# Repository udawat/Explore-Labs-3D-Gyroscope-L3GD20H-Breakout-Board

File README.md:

# Explore Labs 3D Gyroscope L3GD20H Breakout Board
## Overview

[Explore Labs 3D Gyroscope L3GD20H Breakout Board](http://www.explorelabs.com/explore-labs-3d-gyroscope-l3gd20h-breakout-board-5v-ready-with-voltage-regulator "Explore Labs 3D Gyroscope L3GD20H Breakout Board") is based on ST L3GD20H three-axis gyroscope, which measures the angular rates of rotation about the roll (X), pitch (Y), and yaw (Z) axes. Angular velocity measurements with a configurable range of ±245°/s, ±500°/s, or ±2000°/s can be read through a digital I2C or SPI interface.

The carrier board includes a low-dropout linear voltage regulator that provides the 3.3 V required by the L3GD20H, which allows the sensor to be powered from 2.5 V to 5.5 V. The regulator output is available on the 3Vo pin which can supply approx. 150 mA to external devices.

The breakout board also includes a circuit that shifts the two I2C lines or all four SPI lines (clock, data-in/out and chip select) to the same logic voltage level as the supplied VIN, making it simple to interface the board with 5V systems; and the board’s 0.1″ pin spacing makes it easy to use with standard solderless breadboards and 0.1″ perfboards. The board ships fully populated with its SMD components, including the L3GD20H, as shown in the product picture.

## Features of Explore Labs 3D Gyroscope L3GD20H Breakout Board:
* Wide supply voltage - 2.5V to 5V
* Level shifted IO lines for easy interfacing to high voltage boards like Arduino Uno, Mega, Leonardo, etc.
* All pins of the L3GD20H sensor are available like INT1, INT2 (DRDY) and DEN (Data Enable)
* Layout takes care of keeping the area below the sensor free from any active current carrying trace or a power or ground plane
* Capacitors with low ESR characteristics are used for decoupling on both VDD and VDDIO power inputs
* Open Source Hardware
* Designed, Assembled and Made in India

## Features of L3GD20H sensor IC:
* Extended operating temperature range (from -40 °C to 85 °C)
* Low power consumption
* Embedded power-down
* Sleep mode
* Fast turn-on and wake-up
* Three selectable full scales up to 2000 dps (degrees per second)
* 16 bit rate value data output
* 8 bit temperature data output
* I2C/SPI digital output interface
* 2 dedicated lines (1 interrupt, 1 data ready)
* User enable integrated high-pass filters
* Embedded temperature sensor
* Embedded 32 levels of 16 bit data output FIFO
* High shock survivability

## Specifications:
* Input Voltage: 2.5V to 5V
* 5V Ready IOs: Level shifted IO lines for easy interfacing to incompatible voltage boards
* Digital Output: Inter Integrated Circuit (I2C/IIC) or Serial Peripheral Interface (SPI)
* Regulator Pin - Provides 3.3V Out at 150mA (when 3.6V < VIN < 5V) else provides voltage ~equal to VIN
* Dimensions: 20.4 mm x 20 mm
* Weight: 2 grams

## Applications:
* Gaming and virtual reality input devices
* Motion control with MMI (man-machine interface)
* GPS navigation systems
* Appliances and robotics

## Output Format:
Provides individual readings for each axis in degrees per decond (dps). These readings may be used separately or together with an Accelerometer for 3D calculations like calculating euler angles (roll, pitch, yaw) and other complex orientation calculationsfor Inertial Measurement Units (IMU).

## Pinout Table for Explore Labs 3D Gyroscope L3GD20H Breakout Board
|Pin|5V Safe?   |Function|
|---|-----------|--------|
|VIN|Yes|**Input Voltage** Pin: 2.5V to 5.0V (depending on Master device being used as mentioned in later connection sections and tables below)|
|3Vo|Not Applicable|This is the output pin of the onboard 3.3V Voltage Regulator. It provides a clean and regulated 3.3V output to the sensor IC. It can also be used by the user to provide power to external devices or sensors. Maximum current that can be sourced easily would be approximately 125mA to 150mA after leaving some room for the on board sensor IC|
|GND|Not Applicable|Ground Connection. Connect this pin to the master device's ground pin or to any externally powered devices from onboard regulator|
|SDI/SDA|Yes. Bidirectional MOSFET with 4K7 pull-ups|This pin has dual functions - **Serial Data Input** (for SPI) or **Serial Data** (for I2C). In case of SPI, it can also be called as Master Out Slave In (MOSI)|
|SCK/SCL|Yes. Bidirectional MOSFET with 4K7 pull-ups|This pin is the **Serial Clock** input pin. It is common for both SPI and I2C interfaces|
|SDO/ADR|Yes. Only a 4K7 pull-up resistor needed as this is an output pin|This pin has dual functions - **Serial Data Output** (for SPI) or **Address Select** (for I2C). Also called as SA0. In case of SPI, it can also be called as Master In Slave Out (MOSI). In case of I2C, this pin may be pulled LOW or grounded for selecting an alternate address to avoid address conflicts with similar I2C devices. The change will have to be updated in code as well. Leave unconnected if no change in address required for I2C|
|CS|Yes. Bidirectional MOSFET with 4K7 pull-ups|**Chip Select** or Slave Select pin. By default, it is pulled HIGH using an onboard 4K7 pull-up resistor. This sets the default mode of communication for the sensor IC as I2C. For SPI, this pin acts as the chip select pin to communicate with an SPI master device. Leave unconnected when using I2C|
|DEN|No. Take proper care when interfacing with devices that have higher voltage levels. This pin is not 5V tolerant!|**Data Enable** input pin. The L3GD20H allows external trigger level recognition through enabling the EXTRen (bit7) and LVLen (bit6) bits in CTRL2 (21h) register and the IMPen (bit3) bit of CTRL4 register. Three different modes can be used: level-sensitive, pulse-sensitive and edge-sensitive trigger. More detailed explanation can be found in [Section 3.5 of ST Application Note AN4506](http://www.st.com/resource/en/application_note/dm00119037.pdf "ST Application Note - L3GD20H: 3-axis digital output gyroscope")|
|INT1|No|Interrupt output pin. The L3GD20H interrupt signal can be configured in a very flexible way allowing to recognize independent rotations of the X, Y and Z-axis. That signal can be driven to the INT1 pin. The device may be configured to generate interrupt signals by detecting an independent wake-up event. Thresholds and timing of the interrupt generator are programmable by the end user on the fly. More detailed explanation can be found in [Section 5 of ST Application Note AN4506](http://www.st.com/resource/en/application_note/dm00119037.pdf "ST Application Note - L3GD20H: 3-axis digital output gyroscope")|
|INT2|No|Second Interrupt output pin. This pin is dedicated to DRDY and FIFO interrupts. **DRDY Interrupt**: The device may be configured to have one HW signal to determine when a new set of measurement data is available for reading. This signal is represented by the XYZDA bit of the STATUS register. The signal can be driven to the DRDY/INT2 pin. **FIFO Interrupt**: The device may be configured to generate an interrupt on FIFO Threshold, FIFO Overrun or FIFO Empty event. For more details, refer to above application note from ST. More detailed explanation can be found in [Section 3.3 and Section 5.1 of ST Application Note AN4506](http://www.st.com/resource/en/application_note/dm00119037.pdf "ST Application Note - L3GD20H: 3-axis digital output gyroscope")|

## Connections with various development boards are explained below:

The carrier board supports both I2C as well as SPI method of communication with a host microcontroller. The communication mode is selected by pulling the CS pin HIGH or LOW. By default, the CS pin is pulled HIGH through a 4.7 kΩ resistor on the board. This makes I2C communication the default method to talk to this carrier board.

**I2C Communication**: By default, I2C communication is implemented. The Explore Labs 3D Gyroscope L3GD20H Breakout Board can be configured and its angular velocity readings can be queried through the I2C bus. Level shifters on the I2C clock (SCL) and data (SDA) lines enable I2C communication with microcontrollers operating at the same voltage as VIN (2.5V to 5V). A detailed explanation of the I2C interface on the L3GD20H can be found in its [datasheet][1] and more detailed information about I2C Protocol in general can be found in [NXP’s I2C-bus specification manual][2].

**I2C Address**: In I2C mode, the gyro’s 7-bit slave address has its least significant bit (LSb) determined by the voltage on the SDO/ADR pin. The carrier board pulls SDO/ADR HIGH through a 4.7 kΩ resistor, making the LSb 1 and setting the slave address to 1101011b (0x6B). This is the default device address in I2C mode (same address as the previous generation L3GD20). If SDO/ADR pin is connected to ground, LSb value is ‘0’ which changes the device address to 1101010b (0x6A). This solution permits to connect and address two different gyroscopes to the same I2C bus.

**Arduino Uno with I2C Interface**
* Sensor VIN - Arduino Uno 5V
* Sensor GND - Arduino Uno GND
* Sensor SDI/SDA - Arduino Uno Analog Input Pin A4 or SDA
* Sensor SCK/SCL - Arduino Uno Analog Input Pin A5 or SCL

**Raspberry Pi (all models) with I2C Interface**
* Sensor VIN - Raspberry Pi 3.3V on Pin 1 or 17
* Sensor GND - Raspberry Pi GND
* Sensor SDI/SDA - Raspberry Pi SDA1 (I2C) on Pin 3 or GPIO2
* Sensor SCK/SCL - Raspberry Pi SCL1 (I2C) on Pin 5 or GPIO3

**BeagleBone Black with I2C Interface**
* Sensor VIN - BeagleBone Black 3.3V
* Sensor GND - BeagleBone Black GND
* Sensor SDI/SDA - BeagleBone Black I2C2_SDA (Pin 20) on Header P9
* Sensor SCK/SCL - BeagleBone Black I2C2_SCL (Pin 19) on Header P9

## Connecting Explore Labs 3D Gyroscope L3GD20H Breakout Board using I2C (Inter Integrated Circuit) Interface
|L3GD20H|Arduino Uno|Arduino Mega|Arduino Leonardo|Arduino Due|Genuino Zero|Genuino 101|Arduino MKR1000|Raspberry Pi|BeagleBone Black|
|---|---|---|---|---|---|---|---|---|---|
|**VIN**|5V|5V|5V|3.3V|3.3V|VCC (3.3V)|3.3V|3.3V|3.3V|
|**GND**|GND|GND|GND|GND|GND|GND|GND|GND|GND|
|**SDI/SDA**|A4 or SDA|Pin 20 (SDA)|Pin 2 (SDA)|Pin 20 (SDA)|SDA|SDA|Pin 12 (SDA)|Pin 3 (SDA1) or GPIO2|Pin 20 (I2C2_SDA)|
|**SCK/SCL**|A5 or SCL|Pin 21 (SCL)|Pin 3 (SCL)|Pin 21 (SCL)|SCL|SCL|Pin 11 (SCL)|Pin 5 (SCL1) or GPIO3|Pin 19 (I2C2_SCL)|

## SPI Communication:
To use the L3GD20H in SPI mode, CS pin must be driven low (connected to GND). A minimum of four logic connections are used viz., SDI, SCK, SDO and CS. These should be connected to an SPI bus operating at the same logic level as VIN. The SPI interface operates in 4-wire mode by default, with SDI and SDO on separate pins. In the default 4-wire mode, the sensor transmits data to the SPI master on a dedicated data out (SDO) line. If the SPI interface is configured to use 3-wire mode instead, the SDI line doubles as SDO and is driven by the L3GD20H when it transmits data to the master. A detailed explanation of the SPI interface on the L3GD20H can be found in its [datasheet][1].

**Arduino Uno with Serial Peripheral Interface (SPI)**
* Sensor VIN - Arduino Uno 5V
* Sensor GND - Arduino Uno GND
* Sensor SDI/SDA - Arduino Uno Digital Pin 11 or MOSI (Master Out Slave In)
* Sensor SCK/SCL - Arduino Uno Digital Pin 13 or SCK (Serial Clock)
* Sensor SDO/ADR - Arduino Uno Digital Pin 12 or MISO (Master In Slave Out)
* Sensor CS - Arduino Uno Digital Pin 10 or SS (Slave Select or Chip Select)

**Raspberry Pi (all models) with Serial Peripheral Interface (SPI)**
* Sensor VIN - Raspberry Pi 3.3V on Pin 1 or 17
* Sensor GND - Raspberry Pi GND
* Sensor SDI/SDA - Raspberry Pi `MOSI` (SPI) on Pin 19 or GPIO10
* Sensor SCK/SCL - Raspberry Pi `SCLK` (SPI) on Pin 23 or GPIO11
* Sensor SDO/ADR - Raspberry Pi `MISO` (SPI) on Pin 21 or GPIO9
* Sensor CS - Raspberry Pi `CE0_N` (SPI) on Pin 24 or GPIO8

**BeagleBone Black with Serial Peripheral Interface (SPI)**
* Sensor VIN - BeagleBone Black 3.3V
* Sensor GND - BeagleBone Black GND
* Sensor SDI/SDA - BeagleBone Black `SPI0_D0` (Pin 21) on Header P9
* Sensor SCK/SCL - BeagleBone Black `SPI0_SCLK` (Pin 22) on Header P9
* Sensor SDO/ADR - BeagleBone Black `SPI0_D1` (Pin 18) on Header P9
* Sensor CS - BeagleBone Black `SPI0_CS0` (Pin 17) on Header P9

## Connecting Explore Labs 3D Gyroscope L3GD20H Breakout Board using Serial Peripheral Interface (SPI)
|L3GD20H|Arduino Uno|Arduino Mega|Arduino Leonardo|Arduino Due|Genuino Zero|Genuino 101|Arduino MKR1000|Raspberry Pi|BeagleBone Black|
|---|---|---|---|---|---|---|---|---|---|
|**VIN**|5V|5V|5V|3.3V|3.3V|VCC (3.3V)|3.3V|3.3V|3.3V|
|**GND**|GND|GND|GND|GND|GND|GND|GND|GND|GND|
|**SDI/SDA**|Pin 11 or MOSI|Pin 51|Pin 4 (ICSP)|Pin 4 (ICSP)|Pin 4 (ICSP)|Pin 11 (MOSI)|Pin 8 (MOSI)|Pin 19 (`MOSI`) or GPIO10|Pin 21 (`SPI0_D0`)|
|**SCK/SCL**|Pin 13 or SCK|Pin 52|Pin 3 (ICSP)|Pin 3 (ICSP)|Pin 3 (ICSP)|Pin 13|Pin 9|Pin 23 (`SCLK`) or GPIO11|Pin 22 (`SPI0_SCLK`)|
|**SDO/ADR**|Pin 12 or MISO|Pin 50|Pin 1 (ICSP)|Pin 1 (ICSP)|Pin 1 (ICSP)|Pin 12 (MISO)|Pin 10 (MISO)|Pin 21 (`MISO`) or GPIO9|Pin 18 (`SPI0_D1`)|
|**CS**|Pin 10 or SS|Pin 53|Any IO|Any IO|Any IO|Pin 10|Any IO|Pin 24 (`CE0_N`) or GPIO8|Pin 17 (`SPI0_CS0`)|

## ST MEMS Advantage:
It includes a sensing element and an IC interface able to provide the measured angular rate to the external world through digital interface (I2C/SPI). The sensing element is manufactured using a dedicated micromachining process developed by ST to produce inertial sensors and actuators on silicon wafers. The IC interface is manufactured using a CMOS process that allows a high level of integration to design a dedicated circuit which is trimmed to better match the sensing element characteristics.

## Resources:
[1]: http://www.st.com/resource/en/datasheet/l3gd20h.pdf
[Datasheet ST L3GD20H: MEMS motion sensor: 3-axis digital output gyroscope](http://www.st.com/resource/en/datasheet/l3gd20h.pdf "Datasheet ST L3GD20H: MEMS motion sensor: 3-axis digital output gyroscope")

## Code:
Sample code is provided for interfacing the Explore Labs 3D Gyroscope L3GD20H Breakout Board to an Arduino Uno. After choosing the communication method (I2C or SPI), following code examples can be used to test the sensor.

**Using SPI**:
```c
/*
 * Interface Code for Explore Labs 3D Gyroscope L3GD20H Breakout Board
 * and Arduino Uno. This code assumes selected communication method is
 * Serial Peripheral Interface (SPI) and hardware connections are made
 * as follows:
 * 
 * Sensor VIN - Arduino Uno 5V or 3.3V
 * Sensor GND - Arduino Uno GND
 * Sensor SDI/SDA - Arduino Uno Digital Pin 11 or MOSI (Master Out Slave In)
 * Sensor SCK/SCL - Arduino Uno Digital Pin 13 or SCK (Serial Clock)
 * Sensor SDO/ADR - Arduino Uno Digital Pin 12 or MISO (Master In Slave Out)
 * Sensor CS - Arduino Uno Digital Pin 10 or SS (Slave Select or Chip Select)
 * 
 */

#include  // Include Arduino SPI library

#define CTRL1       0x20
#define OUT_X_L     0x28
#define OUT_X_H     0x29
#define OUT_Y_L     0x2A
#define OUT_Y_H     0x2B
#define OUT_Z_L     0x2C
#define OUT_Z_H     0x2D

int8_t readData   = 0x80;
int8_t writeData  = 0x00;
int16_t gx, gy, gz;

const int CS = 10;

void setup() {
  Serial.begin(9600);
  SPI.begin();
  pinMode(CS, OUTPUT);
  writeRegister(CTRL1, 0x0F);
  delay(100);
}

void loop() {
  gx = readRegister(OUT_X_L) <<8 | readRegister(OUT_X_H);
  gy = readRegister(OUT_Y_H) <<8 | readRegister(OUT_Y_L);
  gz = readRegister(OUT_Z_H) <<8 | readRegister(OUT_Z_L);
  Serial.print("Angular Velocity (dps):\t");
  //to convert the raw data to dps, use 8.75 mdps/digit (LSb) for default 250dps
  Serial.print((gx+0), DEC); Serial.print("\t"); //replace +zero with x-axis offset value
  Serial.print((gy+0), DEC); Serial.print("\t"); //replace +zero with y-axis offset value
  Serial.print((gz+0), DEC); Serial.print("\t"); //replace +zero with z-axis offset value
  Serial.println();
  delay(100);
}

int8_t readRegister(int8_t address) {
  
  int8_t buffer = 0;
  digitalWrite(CS, LOW); 
  SPI.transfer(readData | address);
  buffer = SPI.transfer(writeData);
  Serial.print(address, BIN);
  Serial.print(" : ");
  Serial.println(buffer, BIN);
  digitalWrite(CS, HIGH);
  return(buffer);  
}

void writeRegister(int8_t address, int8_t val) {
  
  digitalWrite(CS, LOW);
  SPI.transfer(writeData | address);
  SPI.transfer(val);
  digitalWrite(CS, HIGH);
}
```

**Using I2C**:
```c
/*
 * Interface Code for Explore Labs 3D Gyroscope L3GD20H Breakout Board
 * and Arduino Uno. This code assumes selected communication method is
 * Inter Integrated Circuit (I2C) Interface and hardware connections are made
 * as follows:
 * 
 * Sensor VIN - Arduino Uno 5V or 3.3V
 * Sensor GND - Arduino Uno GND
 * Sensor SDI/SDA - Arduino Uno Analog Input Pin A4
 * Sensor SCK/SCL - Arduino Uno Analog Input Pin A5
 * 
 */
 
#include  // Include Arduino I2C library

#define CTRL1       0x20
#define OUT_X_L     0x28
#define OUT_X_H     0x29
#define OUT_Y_L     0x2A
#define OUT_Y_H     0x2B
#define OUT_Z_L     0x2C
#define OUT_Z_H     0x2D

int8_t readData   = 0x01;
int8_t writeData  = 0x00;
int8_t address    = 0xD6;  //address of L3GD20H with SDO/ADR/SA0 connected to 3Vo.
//int8_t address  = 0xD4;  //address of L3GD20H with SDO/ADR/SA0 connected to GND.

int16_t gx, gy, gz;

void setup() {
  Serial.begin(9600);
  Wire.begin();
  writeRegister(CTRL1, 0x0F);
  delay(100);
}

void loop() {
  gx = readRegister(OUT_X_H) <<8 | readRegister(OUT_X_L);
  gy = readRegister(OUT_Y_H) <<8 | readRegister(OUT_Y_L);
  gz = readRegister(OUT_Z_H) <<8 | readRegister(OUT_Z_L);
  Serial.print("Angular Velocity (dps):\t");
  //to convert the raw data to dps, use 8.75 mdps/digit (LSb) for default 250dps
  Serial.print((gx+0)*0.00875F, DEC); Serial.print("\t"); //replace +zero with x-axis offset value
  Serial.print((gy+0)*0.00875F, DEC); Serial.print("\t"); //replace +zero with y-axis offset value
  Serial.print((gz+0)*0.00875F, DEC); Serial.print("\t"); //replace +zero with z-axis offset value
  Serial.println();
  delay(100);
}

int8_t readRegister(int8_t reg) {
  int8_t buffer = 0;
  Wire.beginTransmission((address | writeData) >>1 ); //slave ID start talking
  Wire.write(reg);
  Wire.endTransmission(0);
  Wire.requestFrom((address | readData) >>1 , 1);
  while(Wire.available() == 0);
  buffer = Wire.read();  
  Wire.endTransmission();
  return(buffer);  
}

void writeRegister(int8_t reg, int8_t val) {
  Wire.beginTransmission((address | writeData) >>1 );
  Wire.write(reg);
  Wire.write(val);
  Wire.endTransmission();
}
```

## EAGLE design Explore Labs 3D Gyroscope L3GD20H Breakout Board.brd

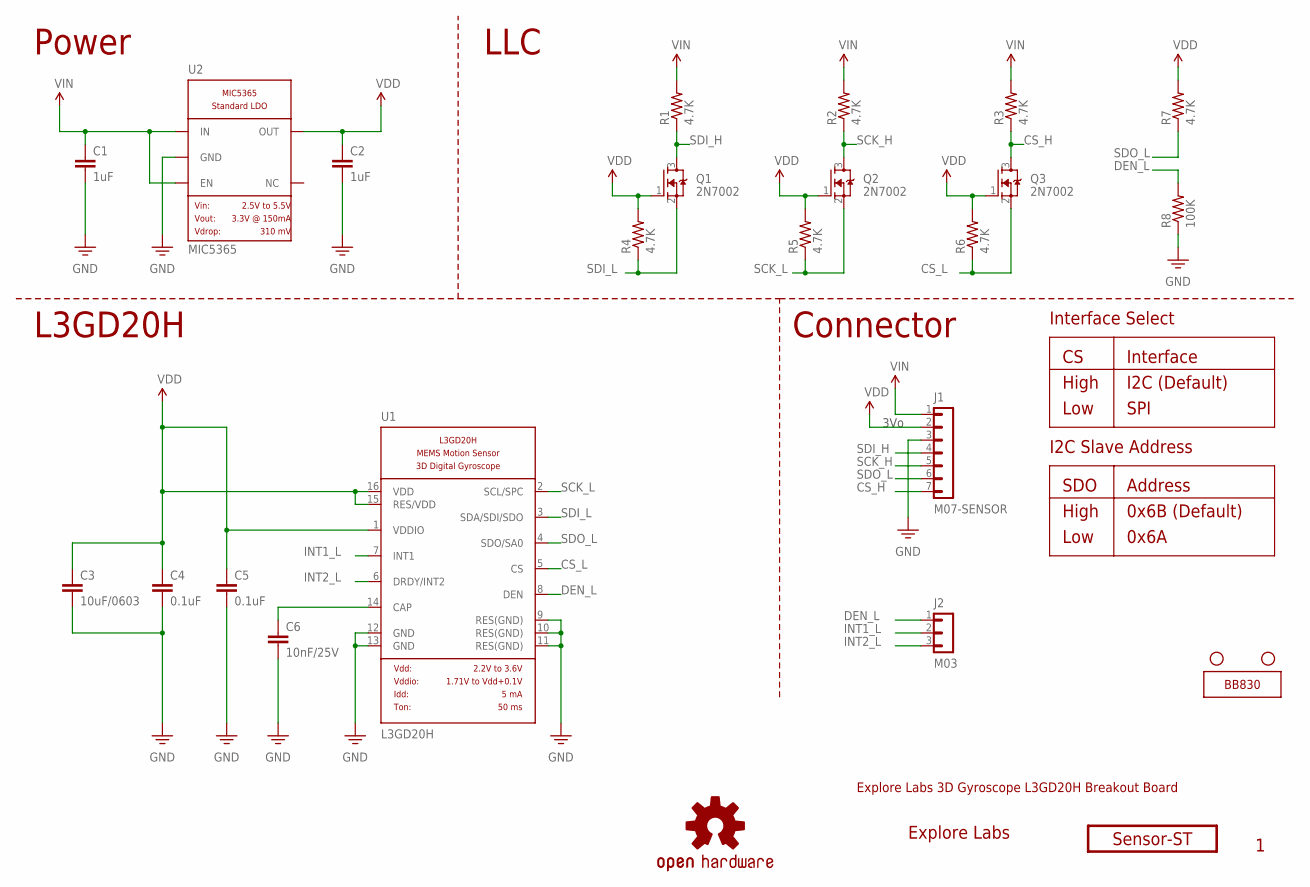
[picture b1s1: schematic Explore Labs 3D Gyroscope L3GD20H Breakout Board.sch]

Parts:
C1, C2: 1uF; 0402-CAP
C3: 10uF/0603; 0603-CAP
C4, C5: 0.1uF; 0402-CAP
C6: 10nF/25V; 0402-CAP
H1, H2: STAND-OFF
J1: M07-SENSOR; 1X07-SENSOR-SPI
J2: M03; 1X03
Q1, Q2, Q3: 2N7002; SOT23
R1, R2, R3, R4, R5, R6, R7: 4.7K; 0402-RES
R8: 100K; 0402-RES
U1: L3GD20H; LGA16
U2: MIC5365; SOT23-LDO
ZZ1: EXPLORE-LABS-LOGO-2-0.25; EXLABS_LOGO_0.25
ZZ2: OSHW-LOGOBOTTOM; OSHW-LOGO-M-BOTTOM
ZZ3: SENSOR-ST
ZZ4: BREADBOARD-830

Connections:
CS_H: J1.7, Q3.3 (D), R3.1
CS_L: Q3.2 (S), R6.1, U1.5 (CS)
DEN_L: J2.1, R8.2, U1.8 (DEN)
GND: C1.2, C2.2, C3.2, C4.2, C5.2, C6.2, J1.3, R8.1, U1.9 (RES(GND)), U1.10 (RES(GND)), U1.11 (RES(GND)), U1.12 (GND), U1.13 (GND), U2.2 (GND)
INT1_L: J2.2, U1.7 (INT1)
INT2_L: J2.3, U1.6 (DRDY/INT2)
unnamed: C6.1, U1.14 (CAP)
SCK_H: J1.5, Q2.3 (D), R2.1
SCK_L: Q2.2 (S), R5.1, U1.2 (SCL/SPC)
SDI_H: J1.4, Q1.3 (D), R1.1
SDI_L: Q1.2 (S), R4.1, U1.3 (SDA/SDI/SDO)
SDO_L: J1.6, R7.1, U1.4 (SDO/SA0)
VDD: C2.1, C3.1, C4.1, C5.1, J1.2, Q1.1 (G), Q2.1 (G), Q3.1 (G), R4.2, R5.2, R6.2, R7.2, U1.1 (VDDIO), U1.15 (RES/VDD), U1.16 (VDD), U2.5 (OUT)
VIN: C1.1, J1.1, R1.2, R2.2, R3.2, U2.1 (IN), U2.3 (EN)

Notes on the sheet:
LLC
Power
3Vo
Connector
I2C (Default)
SPI
High
Low
Interface
0x6B (Default)
0x6A
Address
SDO
Interface Select
I2C Slave Address
L3GD20H
Explore Labs 3D Gyroscope L3GD20H Breakout Board

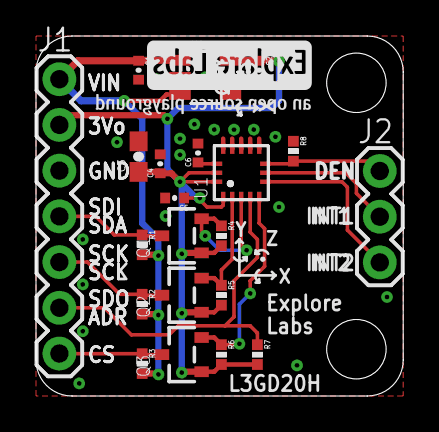
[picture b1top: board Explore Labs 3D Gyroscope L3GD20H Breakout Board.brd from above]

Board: 2 copper layers, 20.4 x 20.0 mm, 27 parts (1 on the bottom side), 14 nets.

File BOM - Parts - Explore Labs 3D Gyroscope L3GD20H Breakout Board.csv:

"Part";"Value";"Device";"Package";"Description";"025";
"C1";"1uF";"CAPACITOR-0402";"0402-CAP";"";"";
"C2";"1uF";"CAPACITOR-0402";"0402-CAP";"";"";
"C3";"10uF/0603";"CAPACITOR-0603";"0603-CAP";"";"";
"C4";"0.1uF";"CAPACITOR-0402";"0402-CAP";"";"";
"C5";"0.1uF";"CAPACITOR-0402";"0402-CAP";"";"";
"C6";"10nF/25V";"CAPACITOR-0402";"0402-CAP";"";"";
"H1";"STAND-OFF";"STAND-OFF";"STAND-OFF";"#4 Stand Off";"";
"H2";"STAND-OFF";"STAND-OFF";"STAND-OFF";"#4 Stand Off";"";
"J2";"M03";"M03";"1X03";"";"";
"J3";"M07-BOSCH";"M07-BOSCH";"1X07-SENSOR-SPI";"Header 7";"";
"LOGO2";"OSHW-LOGOBOTTOM";"OSHW-LOGOBOTTOM";"OSHW-LOGO-M-BOTTOM";"Open Source Hardware Logo This logo indicates the piece of hardware it is found on incorporates a OSHW license and/or adheres to the definition of open source hardware found here: http://freedomdefined.org/OSHW";"";
"Q1";"";"MOSFET-N-2N7002P";"SOT23";"2N7002P";"";
"Q3";"";"MOSFET-N-2N7002P";"SOT23";"2N7002P";"";
"Q4";"";"MOSFET-N-2N7002P";"SOT23";"2N7002P";"";
"R1";"4.7K";"RESISTOR-0402";"0402-RES";"";"";
"R2";"4.7K";"RESISTOR-0402";"0402-RES";"";"";
"R3";"4.7K";"RESISTOR-0402";"0402-RES";"";"";
"R4";"4.7K";"RESISTOR-0402";"0402-RES";"";"";
"R5";"4.7K";"RESISTOR-0402";"0402-RES";"";"";
"R6";"4.7K";"RESISTOR-0402";"0402-RES";"";"";
"R7";"4.7K";"RESISTOR-0402";"0402-RES";"";"";
"R8";"100K";"RESISTOR-0402";"0402-RES";"";"";
"U$1";"SENSOR-ST";"SENSOR-ST";"SENSOR-ST";"";"";
"U$8";"BREADBOARD-830";"BREADBOARD-830";"BREADBOARD-830";"";"";
"U1";"L3GD20H";"L3GD20H";"LGA16";"L3GD20H";"";
"U2";"MIC5365";"MIC5365";"SOT23-LDO";"";"";
"U3";"EXPLORE-LABS-LOGO-2-0.25";"EXPLORE-LABS-LOGO-2-0.25";"EXLABS_LOGO_0.25";"Explore Labs Logo";"0.25";

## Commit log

2016-06-22 update readme
    added description, pinouts, connection tables and syntax highlighting for Arduino code.
2016-06-22 minor edits
    added product images
2016-06-22 initial commit
    added EAGLE schematic, board files, pdf schematic and BOM files
2016-06-22 add schematic image
    schematic in png format
2016-06-22 added code
    Arduino code for I2C and SPI
2016-06-22 clean up
2016-06-22 renamed folders
2016-06-22 minor edits
2016-06-22 edits

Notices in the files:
parts and their libraries:
Explore Labs EAGLE Library: Released under the Creative Commons
Explore Labs EAGLE Library: http://creativecommons.org/licenses/by-sa/4.0
SparkFun-Aesthetics: Licensing: Creative Commons ShareAlike 4.0 International - https://creativecommons.org/licenses/by-sa/4.0
